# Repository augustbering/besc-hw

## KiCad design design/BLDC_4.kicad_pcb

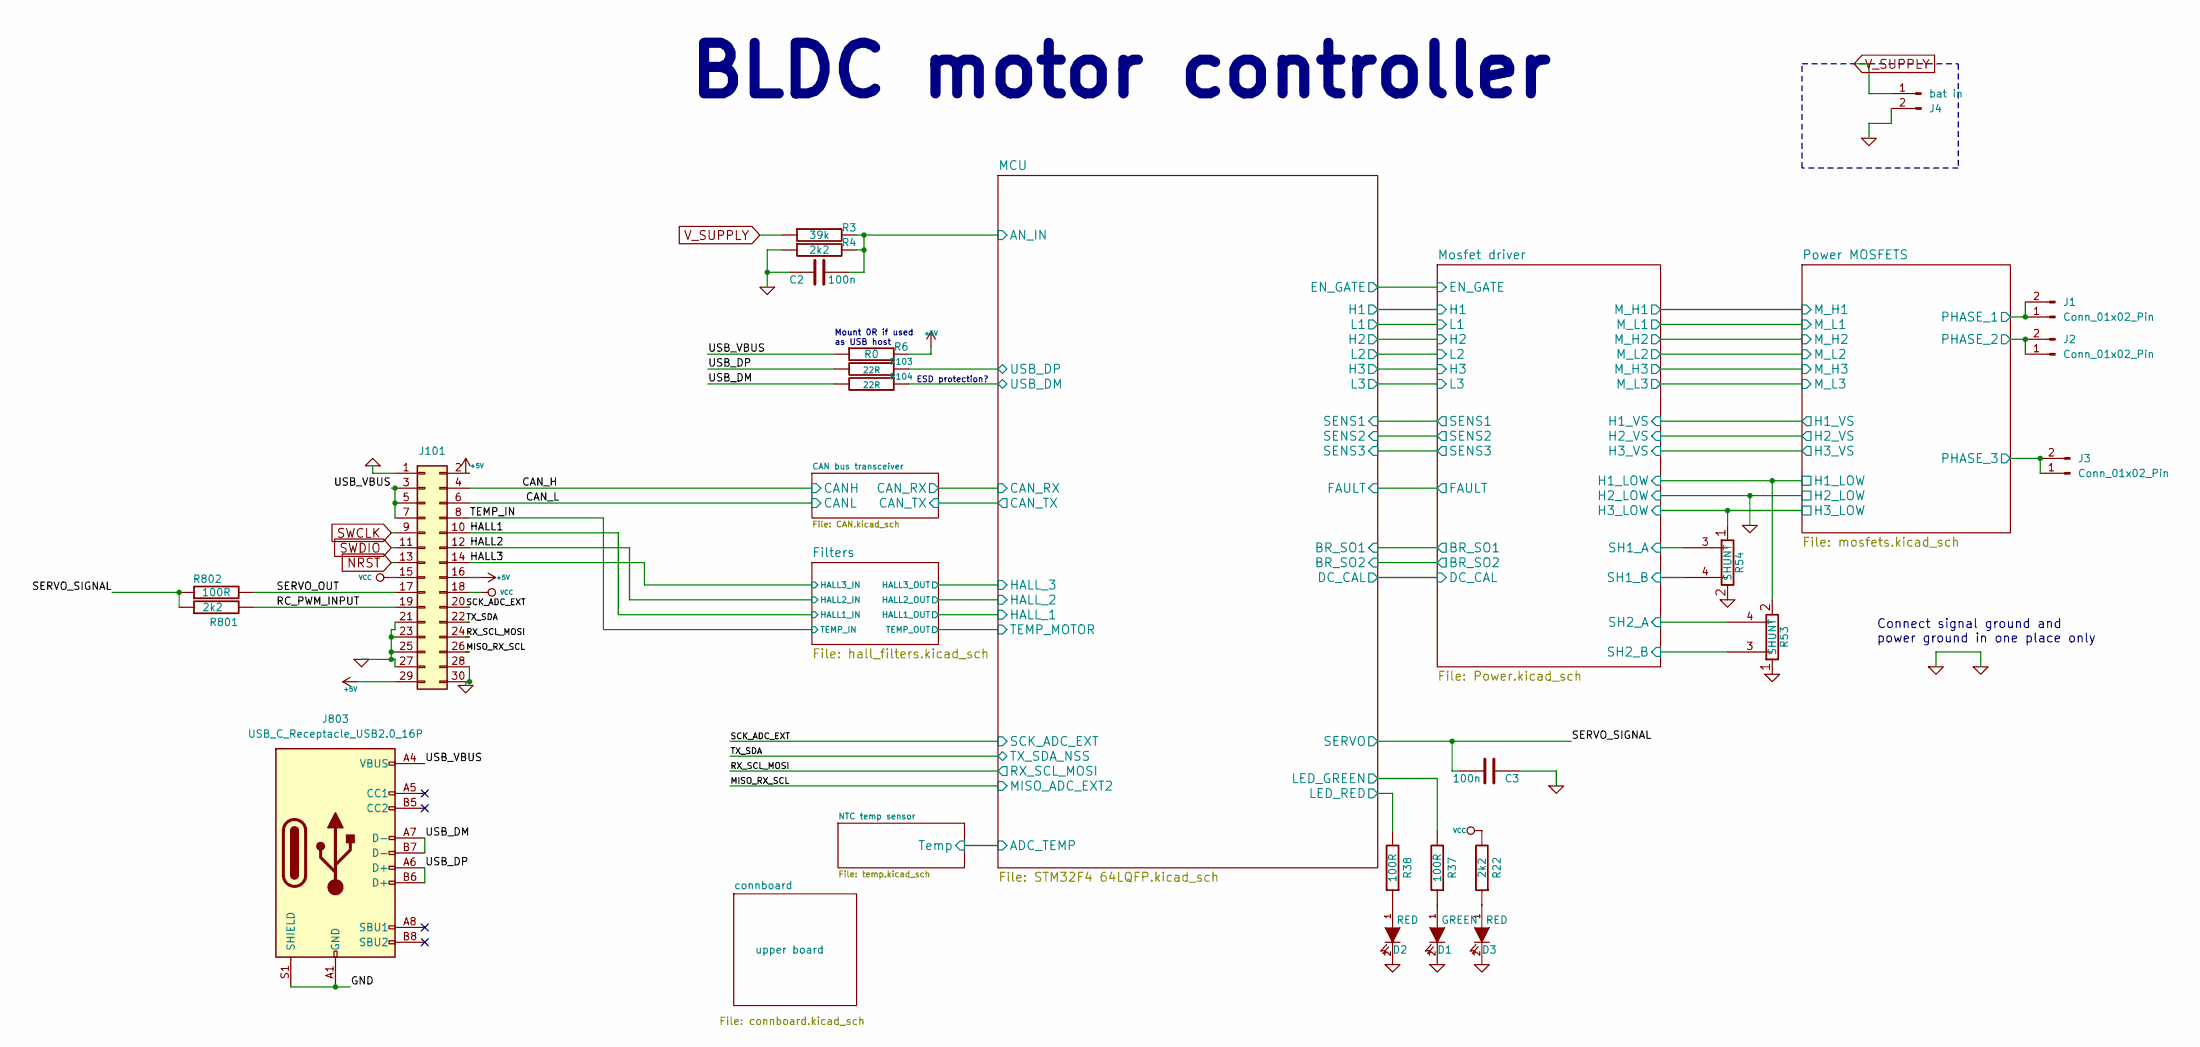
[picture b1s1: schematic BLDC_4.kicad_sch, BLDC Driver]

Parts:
C2, C3: 100n; SMD-0603_c
D1: GREEN; LED-0603; JLCPCB C19273151
D2, D3: RED; LED-0603
J1, J2, J3: Conn_01x02_Pin; AMASS_XT60-F_1x02_P7.20mm_Vertical; JLCPCB C98734
J4: bat in; xt-90 vertical; JLCPCB C3040688
J101: Conn_02x16_Odd_Even; PinHeader_2x15_P2.54mm_Vertical; JLCPCB C169817
J803: USB_C_Receptacle_USB2.0_16P; USB_C_Receptacle_GCT_USB4115-03-C; JLCPCB C183608
R3: 39k; SMD-0603_r
R4, R22, R801: 2k2; SMD-0603_r
R6: R0; SMD-0603_r; JLCPCB C21189
R37, R38, R802: 100R; SMD-0603_r
R53, R54: SHUNT; WSLP2726; JLCPCB C500635
R103, R104: 22R; SMD-0603_r

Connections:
+5V: J101.2, J101.16, J101.29, R6.2; also elsewhere on the board
/CAN_H: J101.4; also elsewhere on the board
/CAN_L: J101.6; also elsewhere on the board
/HALL1: J101.10; also elsewhere on the board
/HALL2: J101.12; also elsewhere on the board
/HALL3: J101.14; also elsewhere on the board
/MCU/AN_IN: C2.2, R3.2, R4.2; also elsewhere on the board
/MCU/LED_GREEN: R37.2; also elsewhere on the board
/MCU/LED_RED: R38.2; also elsewhere on the board
/MCU/USB_DM: R104.1; also elsewhere on the board
/MCU/USB_DP: R103.1; also elsewhere on the board
/MISO_RX_SCL: J101.26; also elsewhere on the board
/Mosfet driver/H1_LOW: R53.2; also elsewhere on the board
/Mosfet driver/H1_VS: J1.1, J1.2; also elsewhere on the board
/Mosfet driver/H2_VS: J2.1, J2.2; also elsewhere on the board
/Mosfet driver/H3_LOW: R54.1; also elsewhere on the board
/Mosfet driver/H3_VS: J3.1, J3.2; also elsewhere on the board
/Mosfet driver/SH1_A: R54.3; also elsewhere on the board
/Mosfet driver/SH1_B: R54.4; also elsewhere on the board
/Mosfet driver/SH2_A: R53.4; also elsewhere on the board
/Mosfet driver/SH2_B: R53.3; also elsewhere on the board
/RC_PWM_INPUT: J101.19, R801.2
/RX_SCL_MOSI: J101.24; also elsewhere on the board
/SCK_ADC_EXT: J101.20; also elsewhere on the board
/SERVO_OUT: J101.17, R802.2
/SERVO_SIGNAL: C3.2, R801.1, R802.1; also elsewhere on the board
/TEMP_IN: J101.8; also elsewhere on the board
/TX_SDA: J101.22; also elsewhere on the board
/USB_DM: J803.A7 (D-), J803.B7 (D-), R104.2
/USB_DP: J803.A6 (D+), J803.B6 (D+), R103.2
/USB_VBUS: J101.3, J101.5, J101.7, J803.A4 (VBUS), J803.A9 (VBUS), J803.B4 (VBUS), J803.B9 (VBUS), R6.1
GND: C2.1, C3.1, D1.2 (K), D2.2 (K), D3.2 (K), J4.2, J101.1, J101.21, J101.23, J101.25, J101.27, J101.28, J101.30, J803.A1 (GND), J803.A12 (GND), J803.B1 (GND), J803.B12 (GND), J803.S1 (SHIELD), R4.1, R53.1, R54.2; also elsewhere on the board
NRST: J101.13; also elsewhere on the board
unnamed: D1.1 (A), R37.1
unnamed: D2.1 (A), R38.1
unnamed: D3.1 (A), R22.1
SWCLK: J101.9; also elsewhere on the board
SWDIO: J101.11; also elsewhere on the board
VCC: J101.15, J101.18, R22.2; also elsewhere on the board
V_SUPPLY: J4.1, R3.1; also elsewhere on the board

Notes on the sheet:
BLDC motor controller
ESD protection?
Mount 0R if used as USB host
Connect signal ground and power ground in one place only

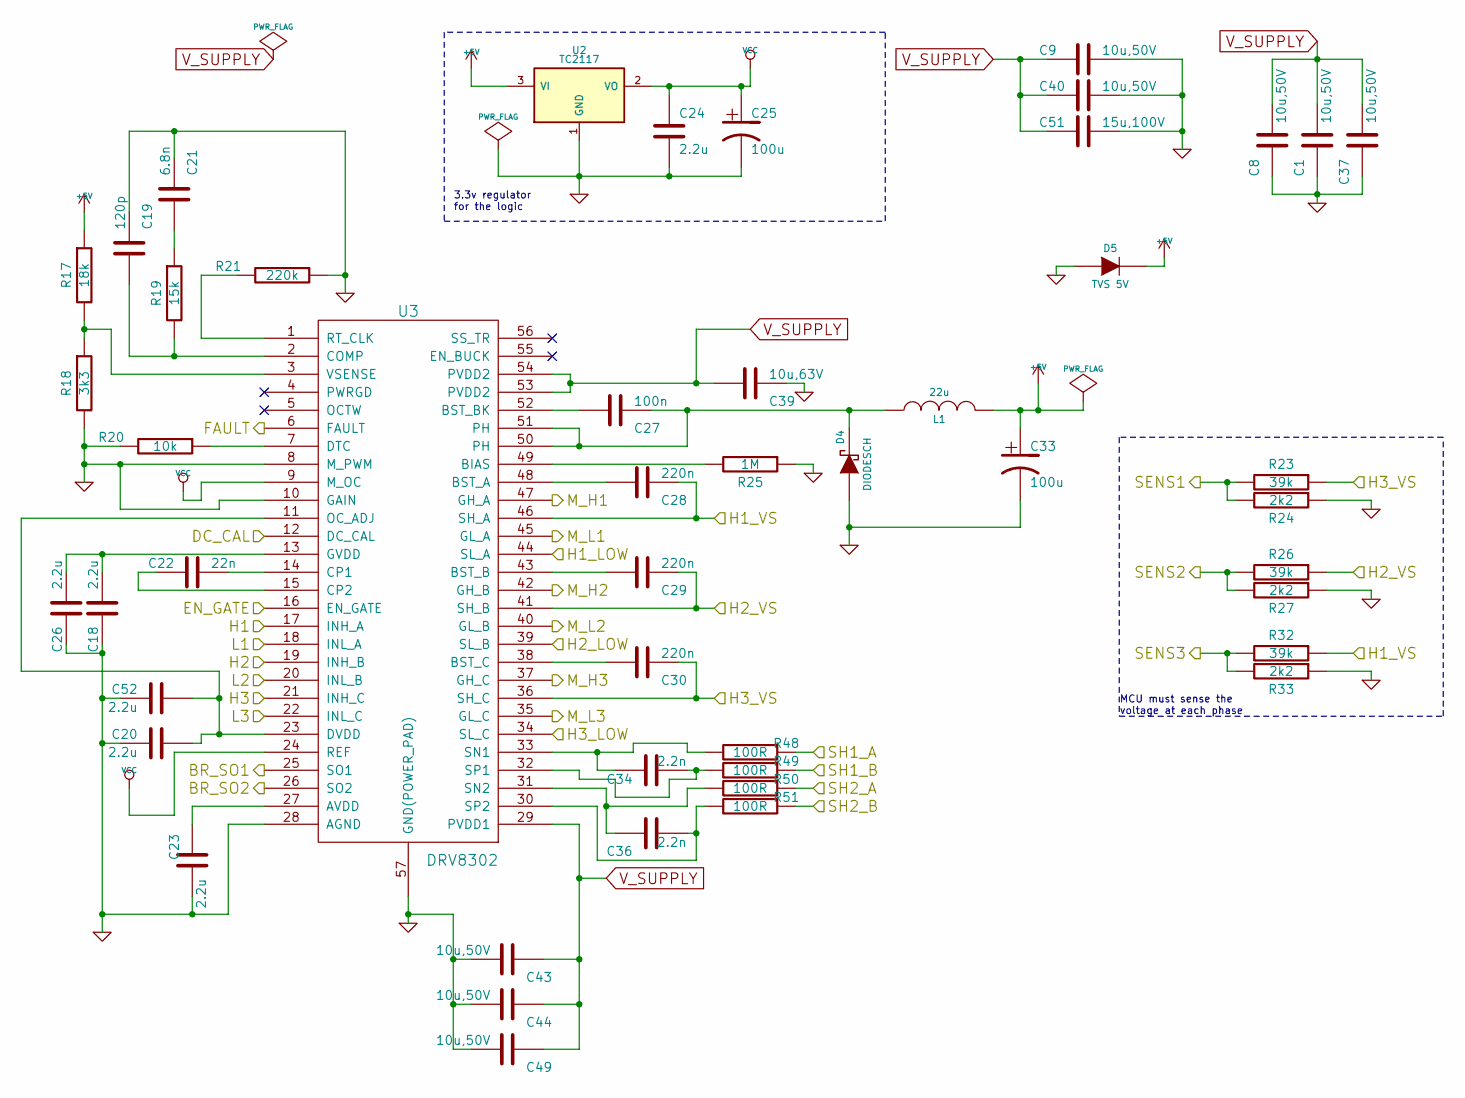
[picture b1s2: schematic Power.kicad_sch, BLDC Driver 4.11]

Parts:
C1, C8, C9, C37, C40, C43, C44, C49: 10u,50V; SMD-1206; JLCPCB C13585
C18, C20, C23, C24, C26, C52: 2.2u; SMD-0603_c; JLCPCB C23630
C19: 120p; SMD-0603_c
C21: 6.8n; SMD-0603_c
C22: 22n; SMD-0603_c
C25, C33: 100u; c_tant_B; JLCPCB C116740
C27: 100n; SMD-0603_c
C28, C29, C30: 220n; SMD-0603_c
C34, C36: 2.2n; SMD-0603_c
C39: 10u,63V; SMD-1206
C51: 15u,100V; c_2220; JLCPCB C5795620
D4: DIODESCH; SMA_Handsoldering; JLCPCB C6807782
D5: TVS 5V; do214ac; JLCPCB C2760868
L1: 22u; inductor_smd_8x5mm; JLCPCB C139488
R17: 18k; SMD-0603_r
R18: 3k3; SMD-0603_r
R19: 15k; SMD-0603_r
R20: 10k; SMD-0603_r
R21: 220k; SMD-0603_r
R23, R26, R32: 39k; SMD-0603_r
R24, R27, R33: 2k2; SMD-0603_r
R25: 1M; SMD-0603_r
R48, R49, R50, R51: 100R; SMD-0603_r
U2: TC2117; SOT-223; JLCPCB C98655
U3: DRV8302; TSSOP-56-PP; JLCPCB C79740

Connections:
+5V: C33.1, D5.2 (K), L1.2, R17.1, U2.3 (VI); also elsewhere on the board
/MCU/BR_SO1: U3.25 (SO1); also elsewhere on the board
/MCU/BR_SO2: U3.26 (SO2); also elsewhere on the board
/MCU/DC_CAL: U3.12 (DC_CAL); also elsewhere on the board
/MCU/EN_GATE: U3.16 (EN_GATE); also elsewhere on the board
/MCU/FAULT: U3.6 (FAULT); also elsewhere on the board
/MCU/H1: U3.17 (INH_A); also elsewhere on the board
/MCU/H2: U3.19 (INH_B); also elsewhere on the board
/MCU/H3: U3.21 (INH_C); also elsewhere on the board
/MCU/L1: U3.18 (INL_A); also elsewhere on the board
/MCU/L2: U3.20 (INL_B); also elsewhere on the board
/MCU/L3: U3.22 (INL_C); also elsewhere on the board
/MCU/SENS1: R23.2, R24.2; also elsewhere on the board
/MCU/SENS2: R26.2, R27.2; also elsewhere on the board
/MCU/SENS3: R32.2, R33.2; also elsewhere on the board
/Mosfet driver/H1_LOW: U3.44 (SL_A); also elsewhere on the board
/Mosfet driver/H1_VS: C28.1, R32.1, U3.46 (SH_A); also elsewhere on the board
/Mosfet driver/H2_VS: C29.1, R26.1, U3.41 (SH_B); also elsewhere on the board
/Mosfet driver/H3_LOW: U3.34 (SL_C); also elsewhere on the board
/Mosfet driver/H3_VS: C30.1, R23.1, U3.36 (SH_C); also elsewhere on the board
/Mosfet driver/M_H1: U3.47 (GH_A); also elsewhere on the board
/Mosfet driver/M_H2: U3.42 (GH_B); also elsewhere on the board
/Mosfet driver/M_H3: U3.37 (GH_C); also elsewhere on the board
/Mosfet driver/M_L1: U3.45 (GL_A); also elsewhere on the board
/Mosfet driver/M_L2: U3.40 (GL_B); also elsewhere on the board
/Mosfet driver/M_L3: U3.35 (GL_C); also elsewhere on the board
/Mosfet driver/SH1_A: R48.1; also elsewhere on the board
/Mosfet driver/SH1_B: R49.1; also elsewhere on the board
/Mosfet driver/SH2_A: R50.1; also elsewhere on the board
/Mosfet driver/SH2_B: R51.1; also elsewhere on the board
GND: C1.1, C8.1, C9.1, C18.2, C19.1, C20.1, C21.1, C23.1, C24.2, C25.2, C26.2, C33.2, C37.1, C39.1, C40.1, C43.2, C44.2, C49.2, C51.1, C52.1, D4.1 (A), D5.1 (A), R18.2, R20.2, R21.1, R24.1, R25.1, R27.1, R33.1, U2.1 (GND), U3.8 (M_PWM), U3.10 (GAIN), U3.28 (AGND), U3.39 (SL_B), U3.57 (GND(POWER_PAD)); also elsewhere on the board
unnamed: C21.2, R19.1
unnamed: C27.1, D4.2 (K), L1.1, U3.50 (PH), U3.51 (PH)
unnamed: C23.2, U3.27 (AVDD)
unnamed: R25.2, U3.49 (BIAS)
unnamed: C28.2, U3.48 (BST_A)
unnamed: C29.2, U3.43 (BST_B)
unnamed: C27.2, U3.52 (BST_BK)
unnamed: C30.2, U3.38 (BST_C)
unnamed: C19.2, R19.2, U3.2 (COMP)
unnamed: C22.1, U3.14 (CP1)
unnamed: C22.2, U3.15 (CP2)
unnamed: R20.1, U3.7 (DTC)
unnamed: C20.2, C52.2, U3.11 (OC_ADJ), U3.23 (DVDD)
unnamed: C18.1, C26.1, U3.13 (GVDD)
unnamed: R21.2, U3.1 (RT_CLK)
unnamed: C34.1, R48.2, U3.33 (SN1)
unnamed: C36.1, R50.2, U3.31 (SN2)
unnamed: C34.2, R49.2, U3.32 (SP1)
unnamed: C36.2, R51.2, U3.30 (SP2)
unnamed: R17.2, R18.1, U3.3 (VSENSE)
VCC: C24.1, C25.1, U2.2 (VO), U3.9 (M_OC), U3.24 (REF); also elsewhere on the board
V_SUPPLY: C1.2, C8.2, C9.2, C37.2, C39.2, C40.2, C43.1, C44.1, C49.1, C51.2, U3.29 (PVDD1), U3.53 (PVDD2), U3.54 (PVDD2); also elsewhere on the board

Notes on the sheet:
MCU must sense the voltage at each phase
3.3v regulator for the logic

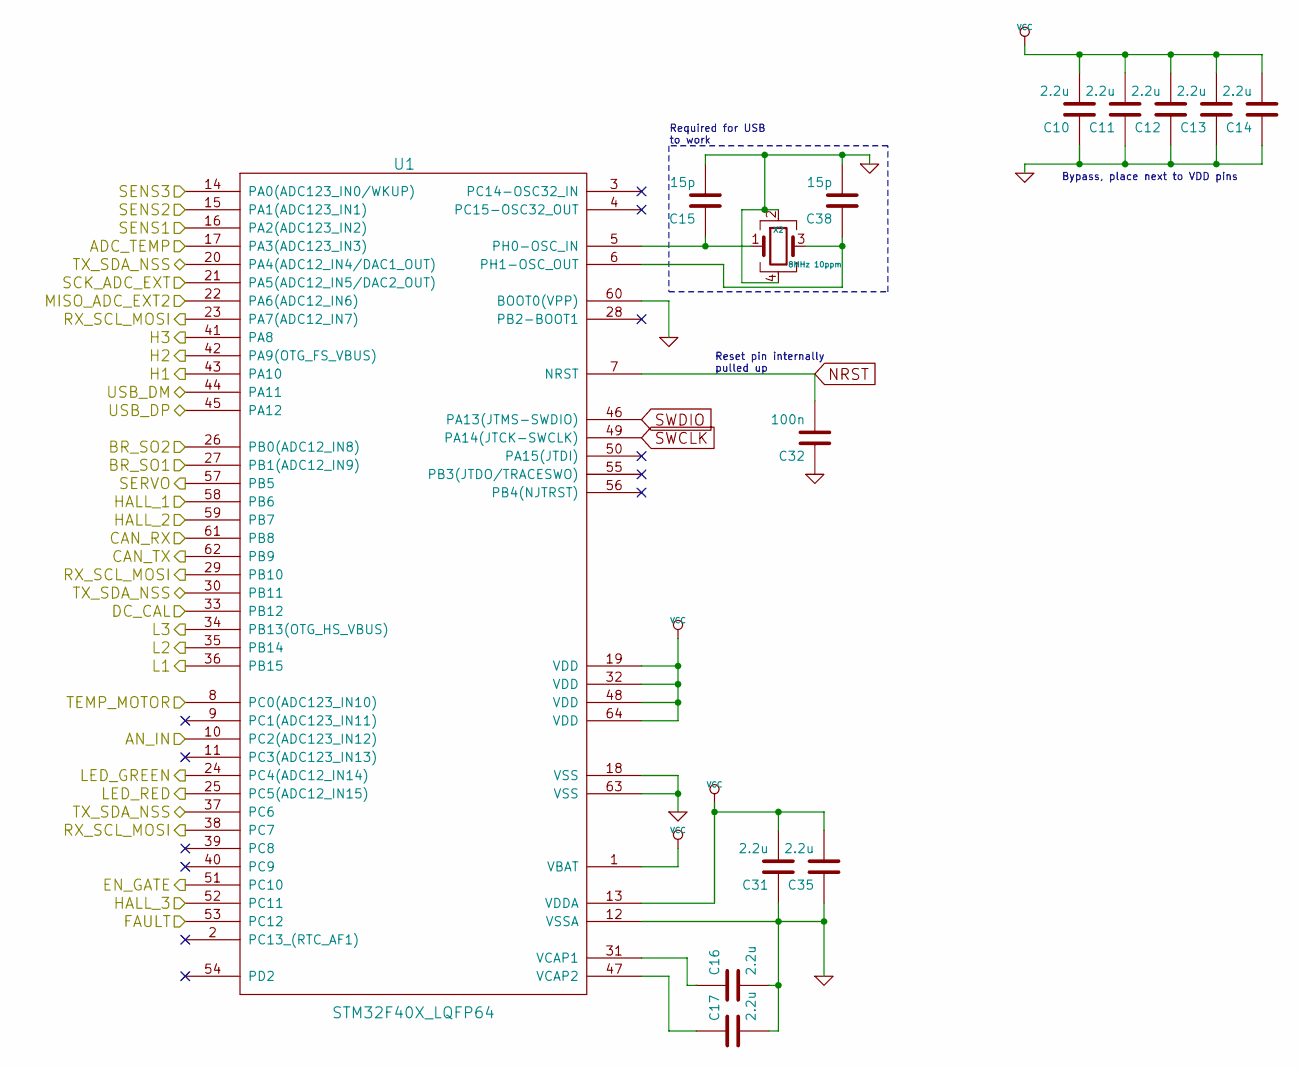
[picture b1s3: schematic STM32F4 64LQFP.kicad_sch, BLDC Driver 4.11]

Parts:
C10, C11, C12, C13, C14, C16, C17, C31, C35: 2.2u; SMD-0603_c; JLCPCB C23630
C15, C38: 15p; SMD-0603_c
C32: 100n; SMD-0603_c
U1: STM32F40X_LQFP64; lqfp64_pad_mod; JLCPCB C15742
X2: 8MHz 10ppm; Crystal_SMD_3225-4Pin_3.2x2.5mm; JLCPCB C5308002

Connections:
/CAN bus transceiver/CAN_RX: U1.61 (PB8); also elsewhere on the board
/CAN bus transceiver/CAN_TX: U1.62 (PB9); also elsewhere on the board
/Filters/HALL1_OUT: U1.58 (PB6); also elsewhere on the board
/Filters/HALL2_OUT: U1.59 (PB7); also elsewhere on the board
/Filters/HALL3_OUT: U1.52 (PC11); also elsewhere on the board
/MCU/ADC_TEMP: U1.17 (PA3(ADC123_IN3)); also elsewhere on the board
/MCU/AN_IN: U1.10 (PC2(ADC123_IN12)); also elsewhere on the board
/MCU/BR_SO1: U1.27 (PB1(ADC12_IN9)); also elsewhere on the board
/MCU/BR_SO2: U1.26 (PB0(ADC12_IN8)); also elsewhere on the board
/MCU/DC_CAL: U1.33 (PB12); also elsewhere on the board
/MCU/EN_GATE: U1.51 (PC10); also elsewhere on the board
/MCU/FAULT: U1.53 (PC12); also elsewhere on the board
/MCU/H1: U1.43 (PA10); also elsewhere on the board
/MCU/H2: U1.42 (PA9(OTG_FS_VBUS)); also elsewhere on the board
/MCU/H3: U1.41 (PA8); also elsewhere on the board
/MCU/L1: U1.36 (PB15); also elsewhere on the board
/MCU/L2: U1.35 (PB14); also elsewhere on the board
/MCU/L3: U1.34 (PB13(OTG_HS_VBUS)); also elsewhere on the board
/MCU/LED_GREEN: U1.24 (PC4(ADC12_IN14)); also elsewhere on the board
/MCU/LED_RED: U1.25 (PC5(ADC12_IN15)); also elsewhere on the board
/MCU/SENS1: U1.16 (PA2(ADC123_IN2)); also elsewhere on the board
/MCU/SENS2: U1.15 (PA1(ADC123_IN1)); also elsewhere on the board
/MCU/SENS3: U1.14 (PA0(ADC123_IN0/WKUP)); also elsewhere on the board
/MCU/USB_DM: U1.44 (PA11); also elsewhere on the board
/MCU/USB_DP: U1.45 (PA12); also elsewhere on the board
/MISO_RX_SCL: U1.22 (PA6(ADC12_IN6)); also elsewhere on the board
/RX_SCL_MOSI: U1.23 (PA7(ADC12_IN7)), U1.29 (PB10), U1.38 (PC7); also elsewhere on the board
/SCK_ADC_EXT: U1.21 (PA5(ADC12_IN5/DAC2_OUT)); also elsewhere on the board
/SERVO_SIGNAL: U1.57 (PB5); also elsewhere on the board
/TEMP_IN: U1.8 (PC0(ADC123_IN10)); also elsewhere on the board
/TX_SDA: U1.20 (PA4(ADC12_IN4/DAC1_OUT)), U1.30 (PB11), U1.37 (PC6); also elsewhere on the board
GND: C10.1, C11.1, C12.1, C13.1, C14.1, C15.2, C16.2, C17.2, C31.1, C32.1, C35.1, C38.2, U1.12 (VSSA), U1.18 (VSS), U1.60 (BOOT0(VPP)), U1.63 (VSS), X2.2, X2.4; also elsewhere on the board
NRST: C32.2, U1.7 (NRST); also elsewhere on the board
unnamed: C15.1, U1.5 (PH0-OSC_IN), X2.1
unnamed: C38.1, U1.6 (PH1-OSC_OUT), X2.3
unnamed: C16.1, U1.31 (VCAP1)
unnamed: C17.1, U1.47 (VCAP2)
SWCLK: U1.49 (PA14(JTCK-SWCLK)); also elsewhere on the board
SWDIO: U1.46 (PA13(JTMS-SWDIO)); also elsewhere on the board
VCC: C10.2, C11.2, C12.2, C13.2, C14.2, C31.2, C35.2, U1.1 (VBAT), U1.13 (VDDA), U1.19 (VDD), U1.32 (VDD), U1.48 (VDD), U1.64 (VDD); also elsewhere on the board

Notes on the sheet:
Reset pin internally pulled up
Bypass, place next to VDD pins
Required for USB to work

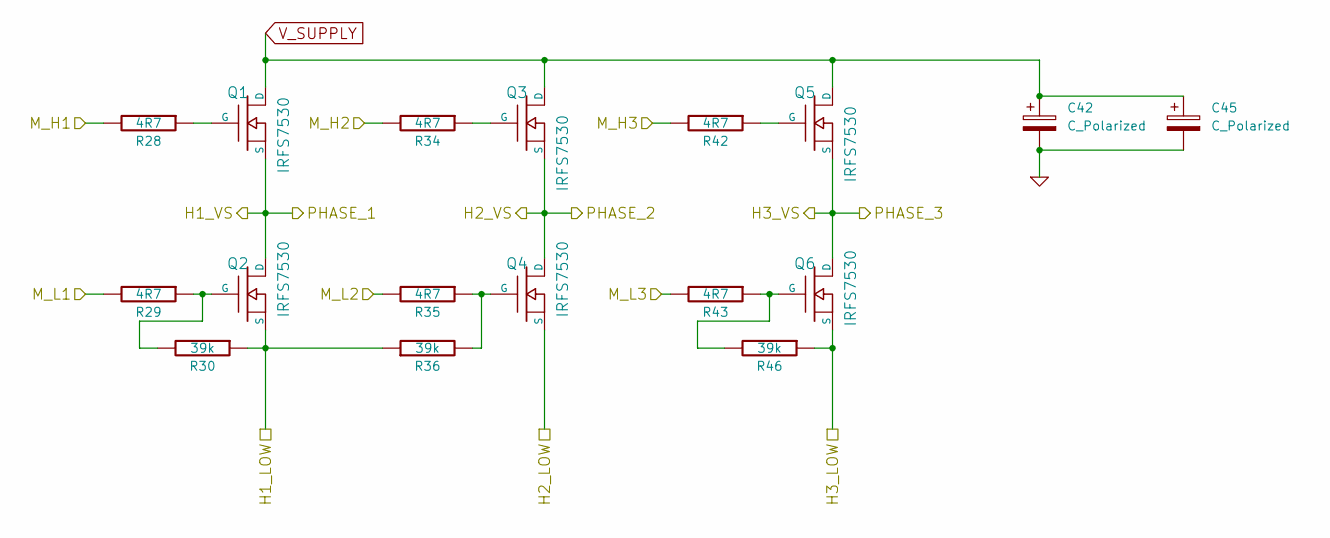
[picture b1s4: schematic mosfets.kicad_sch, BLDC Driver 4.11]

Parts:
C42, C45: C_Polarized; CP_Radial_D13.0mm_P5.00mm; JLCPCB c106632
Q1, Q2, Q3, Q4, Q5, Q6: IRFS7530; D2PAK-7-GDS; JLCPCB C445669
R28, R29, R34, R35, R42, R43: 4R7; SMD-0603_r
R30, R36, R46: 39k; SMD-0603_r

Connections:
/Mosfet driver/H1_LOW: Q2.S, R30.1, R36.1; also elsewhere on the board
/Mosfet driver/H1_VS: Q1.S, Q2.D; also elsewhere on the board
/Mosfet driver/H2_VS: Q3.S, Q4.D; also elsewhere on the board
/Mosfet driver/H3_LOW: Q6.S, R46.1; also elsewhere on the board
/Mosfet driver/H3_VS: Q5.S, Q6.D; also elsewhere on the board
/Mosfet driver/M_H1: R28.2; also elsewhere on the board
/Mosfet driver/M_H2: R34.2; also elsewhere on the board
/Mosfet driver/M_H3: R42.2; also elsewhere on the board
/Mosfet driver/M_L1: R29.2; also elsewhere on the board
/Mosfet driver/M_L2: R35.2; also elsewhere on the board
/Mosfet driver/M_L3: R43.2; also elsewhere on the board
GND: C42.2, C45.2, Q4.S; also elsewhere on the board
unnamed: Q1.G, R28.1
unnamed: Q2.G, R29.1, R30.2
unnamed: Q3.G, R34.1
unnamed: Q4.G, R35.1, R36.2
unnamed: Q5.G, R42.1
unnamed: Q6.G, R43.1, R46.2
V_SUPPLY: C42.1, C45.1, Q1.D, Q3.D, Q5.D; also elsewhere on the board

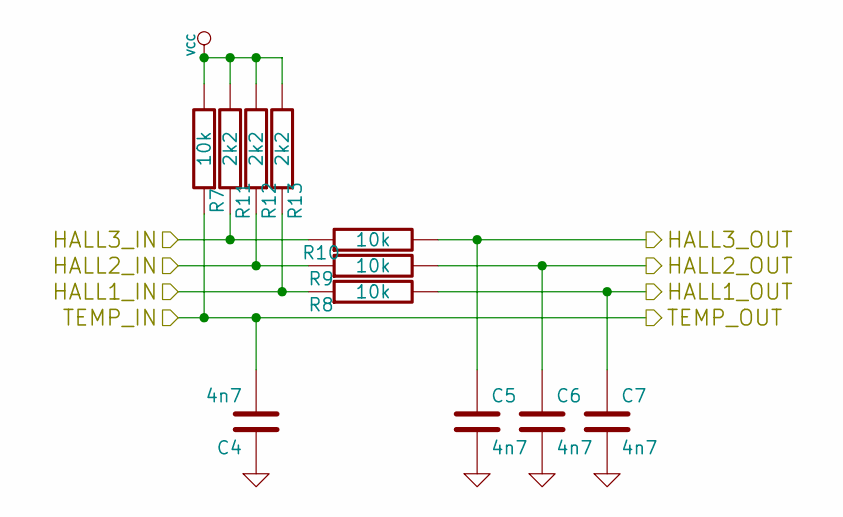
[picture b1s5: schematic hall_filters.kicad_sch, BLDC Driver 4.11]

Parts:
C4, C5, C6, C7: 4n7; SMD-0603_c; JLCPCB C53987
R7, R8, R9, R10: 10k; SMD-0603_r
R11, R12, R13: 2k2; SMD-0603_r

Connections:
/Filters/HALL1_OUT: C7.1, R8.2; also elsewhere on the board
/Filters/HALL2_OUT: C6.1, R9.2; also elsewhere on the board
/Filters/HALL3_OUT: C5.1, R10.2; also elsewhere on the board
/HALL1: R8.1, R13.1; also elsewhere on the board
/HALL2: R9.1, R12.1; also elsewhere on the board
/HALL3: R10.1, R11.1; also elsewhere on the board
/TEMP_IN: C4.2, R7.1; also elsewhere on the board
GND: C4.1, C5.2, C6.2, C7.2; also elsewhere on the board
VCC: R7.2, R11.2, R12.2, R13.2; also elsewhere on the board

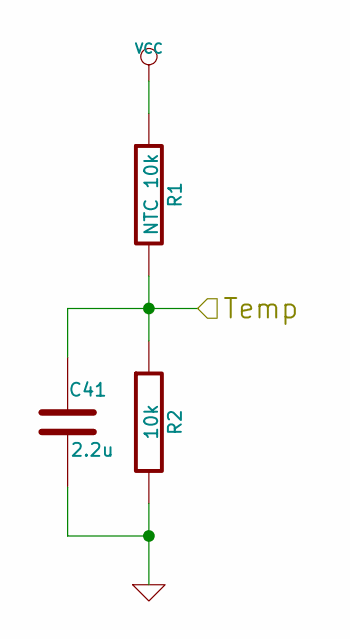
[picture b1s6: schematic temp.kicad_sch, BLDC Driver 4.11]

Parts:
C41: 2.2u; SMD-0603_c; JLCPCB C23630
R1: NTC 10k; SMD-0603_r; mpn NCP18XH103F03RB
R2: 10k; SMD-0603_r

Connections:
/MCU/ADC_TEMP: C41.1, R1.2, R2.1; also elsewhere on the board
GND: C41.2, R2.2; also elsewhere on the board
VCC: R1.1; also elsewhere on the board

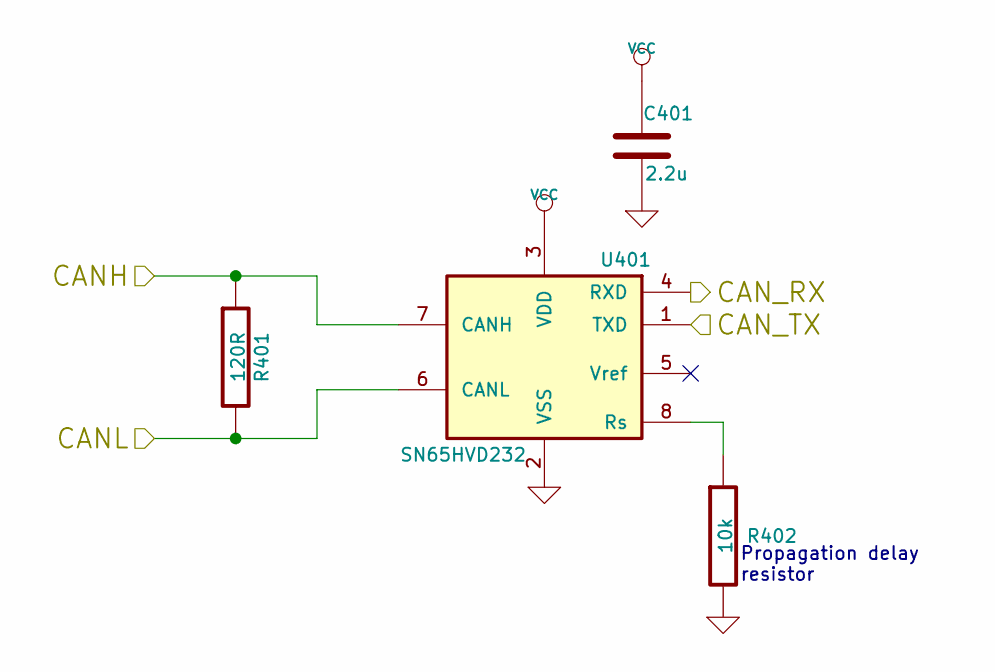
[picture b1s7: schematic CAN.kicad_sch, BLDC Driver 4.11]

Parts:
C401: 2.2u; SMD-0603_c; JLCPCB C23630
R401: 120R; SMD-0603_r
R402: 10k; SMD-0603_r
U401: SN65HVD232; SOIC-8-W; JLCPCB C30530

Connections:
/CAN bus transceiver/CAN_RX: U401.4 (RXD); also elsewhere on the board
/CAN bus transceiver/CAN_TX: U401.1 (TXD); also elsewhere on the board
/CAN_H: R401.1, U401.7 (CANH); also elsewhere on the board
/CAN_L: R401.2, U401.6 (CANL); also elsewhere on the board
GND: C401.2, R402.2, U401.2 (VSS); also elsewhere on the board
unnamed: R402.1, U401.8 (Rs)
VCC: C401.1, U401.3 (VDD); also elsewhere on the board

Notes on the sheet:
Propagation delay resistor

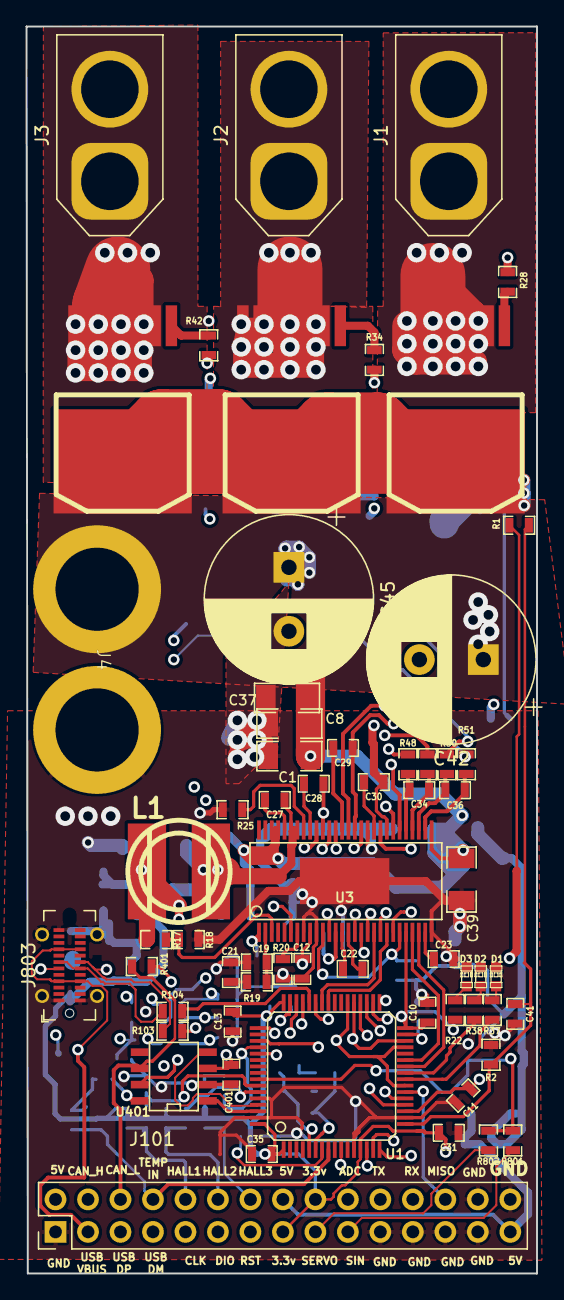
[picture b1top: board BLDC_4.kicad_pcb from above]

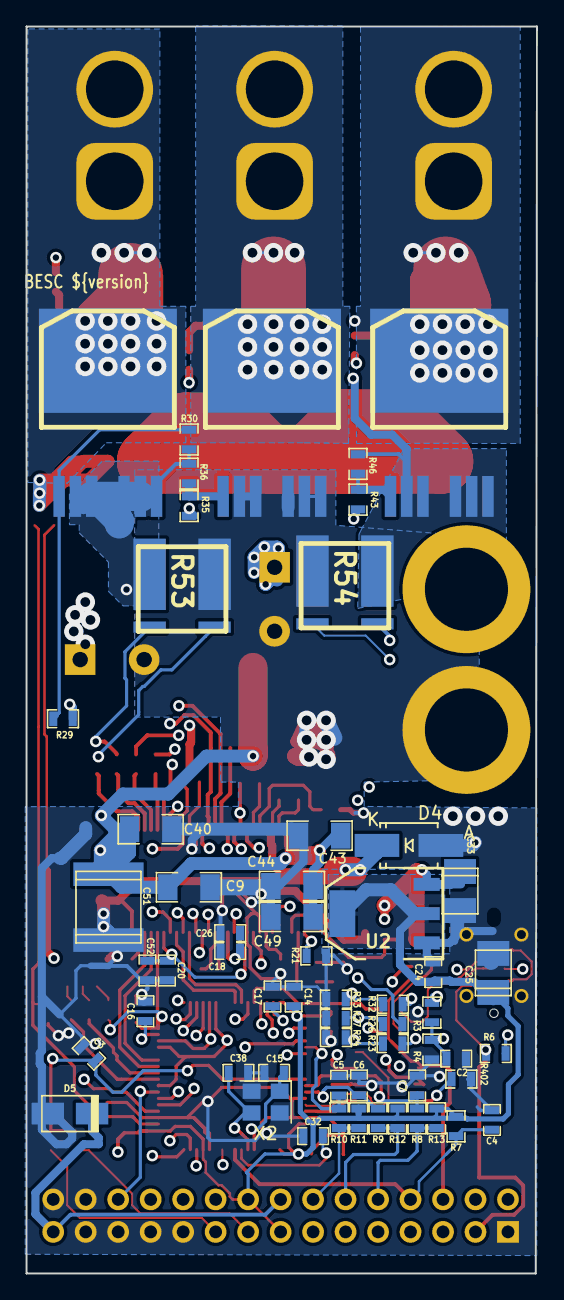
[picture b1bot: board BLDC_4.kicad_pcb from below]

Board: 4 copper layers, 39.9 x 97.5 mm, 120 parts (58 on the bottom side), 97 nets.

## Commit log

2024-09-02 changed to microusb
2024-09-02 work
2024-09-25 first version ordered, working but USB wrong!
2024-09-25 fixed usb and changed to new kicad format
2024-11-07 extended board include input power caps and holes for wires
2025-09-14 v 4.13 produced by jlcpcb
    Some serious issues with usb connectors facing the caps. Working fine
    otherwise
2025-10-13 v4.14 Changed power connectors to XT90 and XT60
2025-10-21 moved a cap to not interfere with the usb connector
2025-10-21 removed some gerber files
2025-10-23 moved the big caps to not interfere with current sense shunts
2025-11-01 moved LEDs to front
